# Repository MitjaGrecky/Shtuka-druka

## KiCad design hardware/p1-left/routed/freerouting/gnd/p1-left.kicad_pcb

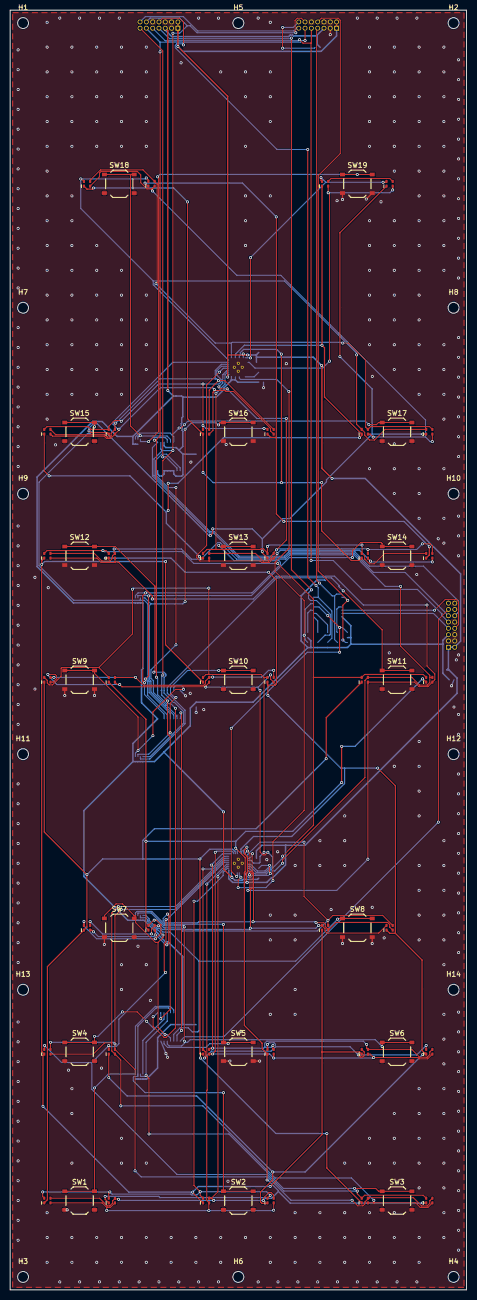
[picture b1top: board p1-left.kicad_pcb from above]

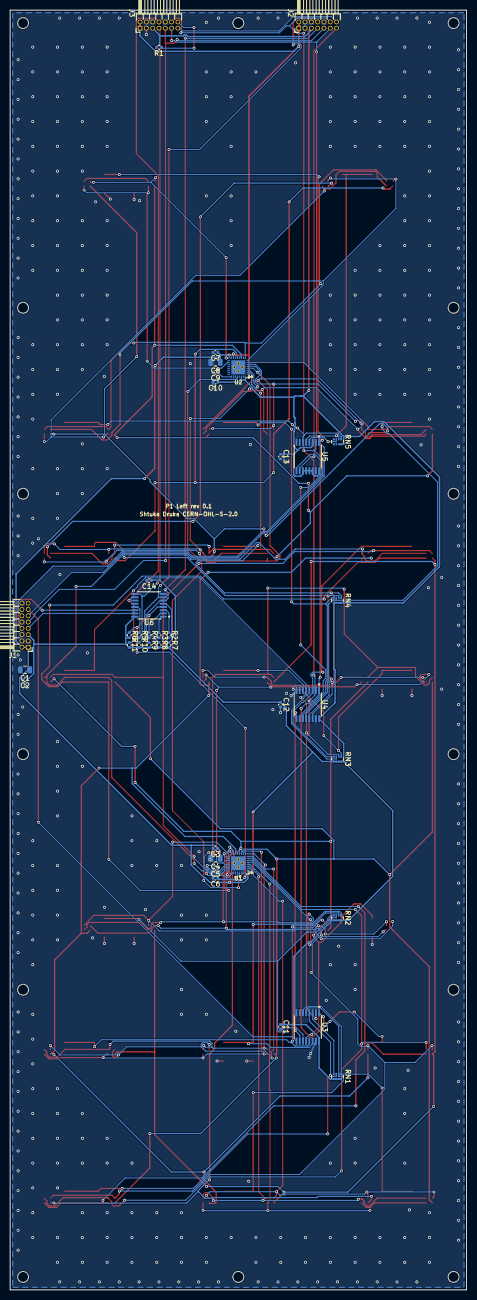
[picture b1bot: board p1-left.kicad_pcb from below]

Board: 2 copper layers, 92.0 x 258.0 mm, 110 parts (39 on the bottom side), 83 nets.

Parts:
C1: 10u; C_0805_2012Metric
C2, C3, C5, C7, C9: 1u; C_0402_1005Metric
C4, C8: 4.7u; C_0805_2012Metric
C6, C10: 1n; C_0402_1005Metric
C11, C12, C13, C14: 100n; C_0402_1005Metric
D1, D2, D3, D4, D5, D6, D7, D8, D9, D10, D11, D12, D13, D14, D15, D16, D17, D18, D19, D20, D21, D22, D23, D24, D25, D26, D27, D28, D29, D30, D31, D32, D33, D34, D35, D36, D37, D38: XL-1615RGBC-RF; LED_RGB_XL-1615RGBC_1.6x1.5mm
H1, H2, H3, H4, H5, H6, H7, H8, H9, H10, H11, H12, H13, H14: M2; MountingHole_2.2mm_M2
J1: Deck bus to P2 2x8 1.27; PinHeader_2x08_P1.27mm_Horizontal
J2: Module bus to M3 2x7 1.27; PinHeader_2x07_P1.27mm_Horizontal
J3: Module bus to W1 2x7 1.27; PinHeader_2x07_P1.27mm_Horizontal
R1, R2: 10k; R_0402_1005Metric
R3, R4, R5: 0; R_0402_1005Metric
R6, R7, R8, R9, R10, R11: 4.7k; R_0402_1005Metric
RN1, RN2, RN3, RN4, RN5: 4x10k; R_Array_Convex_4x0402
SW1, SW2, SW3, SW4, SW5, SW6, SW7, SW8, SW9, SW10, SW11, SW12, SW13, SW14, SW15, SW16, SW17, SW18, SW19: TS-1187A-B-A-B; SW_Push_1P1T_XKB_TS-1187A
U1, U2: LP5864RSMR; VQFN-32-1EP_4x4mm_P0.4mm_EP2.8x2.8mm
U3, U4, U5: 74HC165PW; TSSOP-16_4.4x5mm_P0.65mm
U6: TCA9546APWR; TSSOP-16_4.4x5mm_P0.65mm

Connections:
+3V3: C2.1, C6.1, C10.1, C11.1, C12.1, C13.1, C14.1, J1.5, J2.5, J3.5, R1.2, R2.2, R6.2, R7.2, R8.2, R9.2, R10.2, R11.2, RN1.5, RN1.6, RN1.7, RN1.8, RN2.5, RN2.6, RN2.7, RN2.8, RN3.5, RN3.6, RN3.7, RN3.8, RN4.5, RN4.6, RN4.7, RN4.8, RN5.6, RN5.7, RN5.8, U1.32, U2.30, U2.32, U3.16, U4.16, U5.3, U5.11, U5.12, U5.13, U5.14, U5.16, U6.16
+5V: C1.1, C3.1, C4.1, C7.1, C8.1, J1.1, J1.2, J2.1, J2.2, J3.1, J3.2, U1.1, U1.15, U2.1, U2.15
/A_CS0: D1.1, D2.1, D3.1, D4.1, U1.2
/A_CS1: D1.3, D2.3, D3.3, D4.3, U1.3
/A_CS2: D1.4, D2.4, D3.4, D4.4, U1.4
/A_CS3: D5.1, D6.1, D7.1, D8.1, U1.5
/A_CS4: D5.3, D6.3, D7.3, D8.3, U1.6
/A_CS5: D5.4, D6.4, D7.4, D8.4, U1.7
/A_CS6: D9.1, D10.1, D11.1, D12.1, U1.8
/A_CS7: D9.3, D10.3, D11.3, D12.3, U1.9
/A_CS8: D9.4, D10.4, D11.4, D12.4, U1.10
/A_CS9: D13.1, D14.1, D15.1, D16.1, U1.16
/A_CS10: D13.3, D14.3, D15.3, D16.3, U1.17
/A_CS11: D13.4, D14.4, D15.4, D16.4, U1.18
/A_CS12: D17.1, D18.1, D19.1, D20.1, U1.19
/A_CS13: D17.3, D18.3, D19.3, D20.3, U1.20
/A_CS14: D17.4, D18.4, D19.4, D20.4, U1.21
/A_CS15: D21.1, D22.1, D23.1, D24.1, U1.22
/A_CS16: D21.3, D22.3, D23.3, D24.3, U1.23
/A_CS17: D21.4, D22.4, D23.4, D24.4, U1.24
/A_SW0: D1.2, D5.2, D9.2, D13.2, D17.2, D21.2, U1.11
/A_SW1: D2.2, D6.2, D10.2, D14.2, D18.2, D22.2, U1.12
/A_SW2: D3.2, D7.2, D11.2, D15.2, D19.2, D23.2, U1.13
/A_SW3: D4.2, D8.2, D12.2, D16.2, D20.2, D24.2, U1.14
/A_VCAP: C5.1, U1.25
/BTN1: RN1.1, SW1.1, U3.6
/BTN2: RN1.2, SW2.1, U3.5
/BTN3: RN1.3, SW3.1, U3.4
/BTN4: RN1.4, SW4.1, U3.3
/BTN5: RN2.1, SW5.1, U3.14
/BTN6: RN2.2, SW6.1, U3.13
/BTN7: RN2.3, SW7.1, U3.12
/BTN8: RN2.4, SW8.1, U3.11
/BTN9: RN3.1, SW9.1, U4.6
/BTN10: RN3.2, SW10.1, U4.5
/BTN11: RN3.3, SW11.1, U4.4
/BTN12: RN3.4, SW12.1, U4.3
/BTN13: RN4.1, SW13.1, U4.14
/BTN14: RN4.2, SW14.1, U4.13
/BTN15: RN4.3, SW15.1, U4.12
/BTN16: RN4.4, SW16.1, U4.11
/BTN17: RN5.1, SW17.1, U5.6
/BTN18: RN5.2, SW18.1, U5.5
/BTN19: RN5.3, SW19.1, U5.4
/B_CS0: D25.1, D26.1, D27.1, D28.1, U2.2
/B_CS1: D25.3, D26.3, D27.3, D28.3, U2.3
/B_CS2: D25.4, D26.4, D27.4, D28.4, U2.4
/B_CS3: D29.1, D30.1, D31.1, D32.1, U2.5
/B_CS4: D29.3, D30.3, D31.3, D32.3, U2.6
/B_CS5: D29.4, D30.4, D31.4, D32.4, U2.7
/B_CS6: D33.1, D34.1, D35.1, D36.1, U2.8
/B_CS7: D33.3, D34.3, D35.3, D36.3, U2.9
/B_CS8: D33.4, D34.4, D35.4, D36.4, U2.10
/B_CS9: D37.1, D38.1, U2.16
/B_CS10: D37.3, D38.3, U2.17
/B_CS11: D37.4, D38.4, U2.18
/B_SW0: D25.2, D29.2, D33.2, D37.2, U2.11
/B_SW1: D26.2, D30.2, D34.2, D38.2, U2.12
/B_SW2: D27.2, D31.2, D35.2, U2.13
/B_SW3: D28.2, D32.2, D36.2, U2.14
/B_VCAP: C9.1, U2.25
/MUX_A0: R3.1, U6.1
/MUX_A1: R4.1, U6.2
/MUX_A2: R5.1, U6.13
/MUX_RST: R2.1, U6.3
/SC0: R7.1, U1.28, U2.28, U6.5
/SC1: J2.8, R9.1, U6.7
/SC2: J3.8, R11.1, U6.10
/SCL: J1.8, U6.14
/SD0: R6.1, U1.29, U2.29, U6.4
/SD1: J2.7, R8.1, U6.6
/SD2: J3.7, R10.1, U6.9
/SDA: J1.7, U6.15
/SR_CLK: J1.12, J2.12, J3.12, U3.2, U4.2, U5.2
/SR_END: J3.14, R1.1
/SR_M3: J2.13, U5.10
/SR_OUT: J1.13, U3.9
/SR_Q1: U3.10, U4.9
/SR_Q2: U4.10, U5.9
/SR_W1: J2.14, J3.13
/~INT: J1.9, J2.9, J3.9
/~SR_LOAD: J1.11, J2.11, J3.11, U3.1, U4.1, U5.1
GND: C1.2, C2.2, C3.2, C4.2, C5.2, C6.2, C7.2, C8.2, C9.2, C10.2, C11.2, C12.2, C13.2, C14.2, J1.3, J1.4, J1.6, J1.10, J1.16, J2.3, J2.4, J2.6, J2.10, J3.3, J3.4, J3.6, J3.10, R3.2, R4.2, R5.2, SW1.2, SW2.2, SW3.2, SW4.2, SW5.2, SW6.2, SW7.2, SW8.2, SW9.2, SW10.2, SW11.2, SW12.2, SW13.2, SW14.2, SW15.2, SW16.2, SW17.2, SW18.2, SW19.2, U1.26, U1.27, U1.30, U1.31, U1.33, U2.26, U2.27, U2.31, U2.33, U3.8, U3.15, U4.8, U4.15, U5.8, U5.15, U6.8

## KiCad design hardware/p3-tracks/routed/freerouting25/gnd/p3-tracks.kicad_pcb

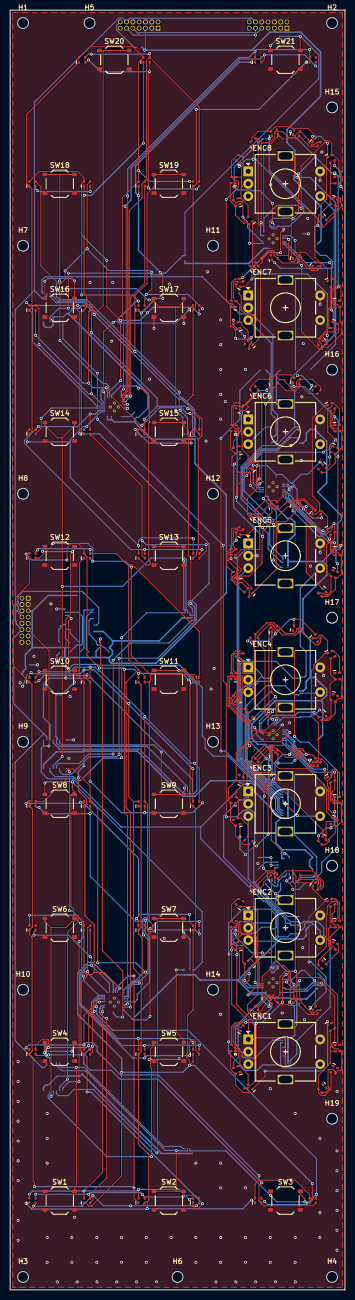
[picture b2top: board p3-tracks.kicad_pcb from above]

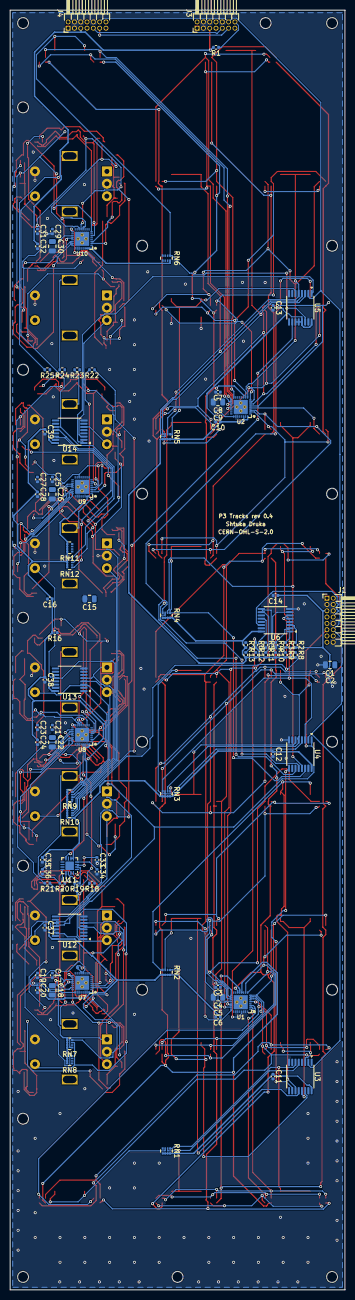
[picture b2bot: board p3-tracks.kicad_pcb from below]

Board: 4 copper layers, 67.5 x 258.0 mm, 276 parts (90 on the bottom side), 226 nets.

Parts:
C1, C15: 10u; C_0805_2012Metric
C2, C3, C5, C7, C9, C16, C17, C19, C21, C23, C25, C27, C29, C31, C35: 1u; C_0402_1005Metric
C4, C8, C18, C22, C26, C30: 4.7u; C_0805_2012Metric
C6, C10, C20, C24, C28, C32: 1n; C_0402_1005Metric
C11, C12, C13, C14, C34, C36, C37, C38, C39: 100n; C_0402_1005Metric
C33: 2.2n; C_0402_1005Metric
D1, D2, D3, D4, D5, D6, D7, D8, D9, D10, D11, D12, D13, D14, D15, D16, D17, D18, D19, D20, D21, D22, D23, D24, D25, D26, D27, D28, D29, D30, D31, D32, D33, D34, D35, D36, D37, D38, D39, D40, D41, D42, D43, D44, D45, D46, D47, D48, D49, D50, D51, D52, D53, D54, D55, D56, D57, D58, D59, D60, D61, D62, D63, D64, D65, D66, D67, D68, D69, D70, D71, D72, D73, D74, D75, D76, D77, D78, D79, D80, D81, D82, D83, D84, D85, D86, D87, D88, D89, D90, D91, D92, D93, D94, D95, D96, D97, D98, D99, D100, D101, D102, D103, D104, D105, D106, D107, D108, D109, D110, D111, D112, D113, D114, D115, D116, D117, D118, D119, D120, D121, D122, D123, D124, D125, D126, D127, D128, D129, D130, D131, D132, D133, D134, D135, D136, D137, D138: XL-1615RGBC-RF; LED_RGB_XL-1615RGBC_1.6x1.5mm
ENC1, ENC2, ENC3, ENC4, ENC5, ENC6, ENC7, ENC8: EC11E smooth, switch; RotaryEncoder_Alps_EC11E-Switch_Vertical_H20mm_Ring
H1, H2, H3, H4, H5, H6, H7, H8, H9, H10, H11, H12, H13, H14, H15, H16, H17, H18, H19: M2; MountingHole_2.2mm_M2
J1: Deck bus to P2 2x8 1.27; PinHeader_2x08_P1.27mm_Horizontal
J3: Module bus to M4 2x7 1.27; PinHeader_2x07_P1.27mm_Horizontal
J4: Module bus to W2 2x7 1.27; PinHeader_2x07_P1.27mm_Horizontal
R1, R2, R16: 10k; R_0402_1005Metric
R3, R4, R5: 0; R_0402_1005Metric
R6, R7, R8, R9, R10, R11, R12, R13: 4.7k; R_0402_1005Metric
R18, R19, R20, R21, R22, R23, R24, R25: 560; R_0402_1005Metric
RN1, RN2, RN3, RN4, RN5, RN6, RN7, RN8, RN9, RN10, RN11, RN12: 4x10k; R_Array_Convex_4x0402
SW1, SW2, SW3, SW4, SW5, SW6, SW7, SW8, SW9, SW10, SW11, SW12, SW13, SW14, SW15, SW16, SW17, SW18, SW19, SW20, SW21: TS-1187A-B-A-B; SW_Push_1P1T_XKB_TS-1187A
U1, U2, U7, U8, U9, U10: LP5864RSMR; VQFN-32-1EP_4x4mm_P0.4mm_EP2.8x2.8mm
U3, U4, U5, U12, U13, U14: 74HC165PW; TSSOP-16_4.4x5mm_P0.65mm
U6: TCA9546APWR; TSSOP-16_4.4x5mm_P0.65mm
U11: CY8CMBR3108-LQXIT; QFN-16-1EP_3x3mm_P0.5mm_EP1.7x1.7mm

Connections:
+3V3: C2.1, C6.1, C10.1, C11.1, C12.1, C13.1, C14.1, C16.1, C20.1, C24.1, C28.1, C32.1, C35.1, C36.1, C37.1, C38.1, C39.1, J1.5, J3.5, J4.5, R1.2, R2.2, R3.2, R6.2, R7.2, R8.2, R9.2, R10.2, R11.2, R12.2, R13.2, R16.2, RN1.5, RN1.6, RN1.7, RN1.8, RN2.5, RN2.6, RN2.7, RN2.8, RN3.5, RN3.6, RN3.7, RN3.8, RN4.5, RN4.6, RN4.7, RN4.8, RN5.5, RN5.6, RN5.7, RN5.8, RN6.8, RN7.5, RN7.6, RN7.7, RN7.8, RN8.5, RN8.6, RN8.7, RN8.8, RN9.5, RN9.6, RN9.7, RN9.8, RN10.5, RN10.6, RN10.7, RN10.8, RN11.5, RN11.6, RN11.7, RN11.8, RN12.5, RN12.6, RN12.7, RN12.8, U1.32, U2.30, U2.32, U3.16, U4.16, U5.11, U5.12, U5.13, U5.16, U6.16, U7.32, U8.30, U8.32, U9.31, U9.32, U10.30, U10.31, U10.32, U11.5, U11.6, U12.16, U13.16, U14.16
+5V: C1.1, C3.1, C4.1, C7.1, C8.1, C15.1, C17.1, C18.1, C21.1, C22.1, C25.1, C26.1, C29.1, C30.1, J1.1, J1.2, J3.1, J3.2, J4.1, J4.2, U1.1, U1.15, U2.1, U2.15, U7.1, U7.15, U8.1, U8.15, U9.1, U9.15, U10.1, U10.15
/A_CS0: D1.1, D2.1, D3.1, D4.1, U1.2
/A_CS1: D1.4, D2.4, D3.4, D4.4, U1.3
/A_CS2: D1.3, D2.3, D3.3, D4.3, U1.4
/A_CS3: D5.1, D6.1, D7.1, D8.1, U1.5
/A_CS4: D5.4, D6.4, D7.4, D8.4, U1.6
/A_CS5: D5.3, D6.3, D7.3, D8.3, U1.7
/A_CS6: D9.1, D10.1, D11.1, D12.1, U1.8
/A_CS7: D9.4, D10.4, D11.4, D12.4, U1.9
/A_CS8: D9.3, D10.3, D11.3, D12.3, U1.10
/A_CS9: D13.1, D14.1, D15.1, D16.1, U1.16
/A_CS10: D13.4, D14.4, D15.4, D16.4, U1.17
/A_CS11: D13.3, D14.3, D15.3, D16.3, U1.18
/A_CS12: D17.1, D18.1, D19.1, D20.1, U1.19
/A_CS13: D17.4, D18.4, D19.4, D20.4, U1.20
/A_CS14: D17.3, D18.3, D19.3, D20.3, U1.21
/A_CS15: D21.1, D22.1, D23.1, D24.1, U1.22
/A_CS16: D21.4, D22.4, D23.4, D24.4, U1.23
/A_CS17: D21.3, D22.3, D23.3, D24.3, U1.24
/A_SW0: D1.2, D5.2, D9.2, D13.2, D17.2, D21.2, U1.11
/A_SW1: D2.2, D6.2, D10.2, D14.2, D18.2, D22.2, U1.12
/A_SW2: D3.2, D7.2, D11.2, D15.2, D19.2, D23.2, U1.13
/A_SW3: D4.2, D8.2, D12.2, D16.2, D20.2, D24.2, U1.14
/A_VCAP: C5.1, U1.25
/BTN1: RN1.1, SW1.1, U3.6
/BTN2: RN1.2, SW2.1, U3.5
/BTN3: RN1.3, SW3.1, U3.4
/BTN4: RN1.4, SW4.1, U3.3
/BTN5: RN2.1, SW5.1, U3.14
/BTN6: RN2.2, SW6.1, U3.13
/BTN7: RN2.3, SW7.1, U3.12
/BTN8: RN2.4, SW8.1, U3.11
/BTN9: RN3.1, SW9.1, U4.6
/BTN10: RN3.2, SW10.1, U4.5
/BTN11: RN3.3, SW11.1, U4.4
/BTN12: RN3.4, SW12.1, U4.3
/BTN13: RN4.1, SW13.1, U4.14
/BTN14: RN4.2, SW14.1, U4.13
/BTN15: RN4.3, SW15.1, U4.12
/BTN16: RN4.4, SW16.1, U4.11
/BTN17: RN5.1, SW17.1, U5.6
/BTN18: RN5.2, SW18.1, U5.5
/BTN19: RN5.3, SW19.1, U5.4
/BTN20: RN5.4, SW20.1, U5.3
/BTN21: RN6.1, SW21.1, U5.14
/B_CS0: D25.1, D26.1, D27.1, D28.1, U2.2
/B_CS1: D25.4, D26.4, D27.4, D28.4, U2.3
/B_CS2: D25.3, D26.3, D27.3, D28.3, U2.4
/B_CS3: D29.1, D30.1, D31.1, D32.1, U2.5
/B_CS4: D29.4, D30.4, D31.4, D32.4, U2.6
/B_CS5: D29.3, D30.3, D31.3, D32.3, U2.7
/B_CS6: D33.1, D34.1, D35.1, D36.1, U2.8
/B_CS7: D33.4, D34.4, D35.4, D36.4, U2.9
/B_CS8: D33.3, D34.3, D35.3, D36.3, U2.10
/B_CS9: D37.1, D38.1, D39.1, D40.1, U2.16
/B_CS10: D37.4, D38.4, D39.4, D40.4, U2.17
/B_CS11: D37.3, D38.3, D39.3, D40.3, U2.18
/B_CS12: D41.1, D42.1, U2.19
/B_CS13: D41.4, D42.4, U2.20
/B_CS14: D41.3, D42.3, U2.21
/B_SW0: D25.2, D29.2, D33.2, D37.2, D41.2, U2.11
/B_SW1: D26.2, D30.2, D34.2, D38.2, D42.2, U2.12
/B_SW2: D27.2, D31.2, D35.2, D39.2, U2.13
/B_SW3: D28.2, D32.2, D36.2, D40.2, U2.14
/B_VCAP: C9.1, U2.25
/CMOD: C33.1, U11.3
/E0_A: ENC1.A, RN7.1, U12.6
/E0_B: ENC1.B, RN7.2, U12.5
/E0_SW: ENC1.S1, RN7.3, U12.4
/E1_A: ENC2.A, RN7.4, U12.3
/E1_B: ENC2.B, RN8.1, U12.14
/E1_SW: ENC2.S1, RN8.2, U12.13
/E2_A: ENC3.A, RN8.3, U12.12
/E2_B: ENC3.B, RN8.4, U12.11
/E2_SW: ENC3.S1, RN9.1, U13.6
/E3_A: ENC4.A, RN9.2, U13.5
/E3_B: ENC4.B, RN9.3, U13.4
/E3_SW: ENC4.S1, RN9.4, U13.3
/E4_A: ENC5.A, RN10.1, U13.14
/E4_B: ENC5.B, RN10.2, U13.13
/E4_SW: ENC5.S1, RN10.3, U13.12
/E5_A: ENC6.A, RN10.4, U13.11
/E5_B: ENC6.B, RN11.1, U14.6
/E5_SW: ENC6.S1, RN11.2, U14.5
/E6_A: ENC7.A, RN11.3, U14.4
/E6_B: ENC7.B, RN11.4, U14.3
/E6_SW: ENC7.S1, RN12.1, U14.14
/E7_A: ENC8.A, RN12.2, U14.13
/E7_B: ENC8.B, RN12.3, U14.12
/E7_SW: ENC8.S1, RN12.4, U14.11
/LA_CS0: D55.1, D56.1, D57.1, D58.1, U7.2
/LA_CS1: D55.4, D56.4, D57.4, D58.4, U7.3
/LA_CS2: D55.3, D56.3, D57.3, D58.3, U7.4
/LA_CS3: D59.1, D60.1, D61.1, D62.1, U7.5
/LA_CS4: D59.4, D60.4, D61.4, D62.4, U7.6
/LA_CS5: D59.3, D60.3, D61.3, D62.3, U7.7
/LA_CS6: D63.1, D64.1, D65.1, D66.1, U7.8
/LA_CS7: D63.4, D64.4, D65.4, D66.4, U7.9
/LA_CS8: D63.3, D64.3, D65.3, D66.3, U7.10
/LA_CS9: D43.1, D44.1, D45.1, D46.1, U7.16
/LA_CS10: D43.4, D44.4, D45.4, D46.4, U7.17
/LA_CS11: D43.3, D44.3, D45.3, D46.3, U7.18
/LA_CS12: D47.1, D48.1, D49.1, D50.1, U7.19
/LA_CS13: D47.4, D48.4, D49.4, D50.4, U7.20
/LA_CS14: D47.3, D48.3, D49.3, D50.3, U7.21
/LA_CS15: D51.1, D52.1, D53.1, D54.1, U7.22
/LA_CS16: D51.4, D52.4, D53.4, D54.4, U7.23
/LA_CS17: D51.3, D52.3, D53.3, D54.3, U7.24
/LA_SW0: D43.2, D50.2, D51.2, D55.2, D62.2, D63.2, U7.11
/LA_SW1: D44.2, D49.2, D52.2, D56.2, D61.2, D64.2, U7.12
/LA_SW2: D45.2, D48.2, D53.2, D57.2, D60.2, D65.2, U7.13
/LA_SW3: D46.2, D47.2, D54.2, D58.2, D59.2, D66.2, U7.14
/LA_VCAP: C19.1, U7.25
/LB_CS0: D79.1, D80.1, D81.1, D82.1, U8.2
/LB_CS1: D79.4, D80.4, D81.4, D82.4, U8.3
/LB_CS2: D79.3, D80.3, D81.3, D82.3, U8.4
/LB_CS3: D83.1, D84.1, D85.1, D86.1, U8.5
/LB_CS4: D83.4, D84.4, D85.4, D86.4, U8.6
/LB_CS5: D83.3, D84.3, D85.3, D86.3, U8.7
/LB_CS6: D87.1, D88.1, D89.1, D90.1, U8.8
/LB_CS7: D87.4, D88.4, D89.4, D90.4, U8.9
/LB_CS8: D87.3, D88.3, D89.3, D90.3, U8.10
/LB_CS9: D67.1, D68.1, D69.1, D70.1, U8.16
/LB_CS10: D67.4, D68.4, D69.4, D70.4, U8.17
/LB_CS11: D67.3, D68.3, D69.3, D70.3, U8.18
/LB_CS12: D71.1, D72.1, D73.1, D74.1, U8.19
/LB_CS13: D71.4, D72.4, D73.4, D74.4, U8.20
/LB_CS14: D71.3, D72.3, D73.3, D74.3, U8.21
/LB_CS15: D75.1, D76.1, D77.1, D78.1, U8.22
/LB_CS16: D75.4, D76.4, D77.4, D78.4, U8.23
/LB_CS17: D75.3, D76.3, D77.3, D78.3, U8.24
/LB_SW0: D67.2, D74.2, D75.2, D79.2, D86.2, D87.2, U8.11
/LB_SW1: D68.2, D73.2, D76.2, D80.2, D85.2, D88.2, U8.12
/LB_SW2: D69.2, D72.2, D77.2, D81.2, D84.2, D89.2, U8.13
/LB_SW3: D70.2, D71.2, D78.2, D82.2, D83.2, D90.2, U8.14
/LB_VCAP: C23.1, U8.25
/LC_CS0: D103.1, D104.1, D105.1, D106.1, U9.2
/LC_CS1: D103.4, D104.4, D105.4, D106.4, U9.3
/LC_CS2: D103.3, D104.3, D105.3, D106.3, U9.4
/LC_CS3: D107.1, D108.1, D109.1, D110.1, U9.5
/LC_CS4: D107.4, D108.4, D109.4, D110.4, U9.6
/LC_CS5: D107.3, D108.3, D109.3, D110.3, U9.7
/LC_CS6: D111.1, D112.1, D113.1, D114.1, U9.8
/LC_CS7: D111.4, D112.4, D113.4, D114.4, U9.9
/LC_CS8: D111.3, D112.3, D113.3, D114.3, U9.10
/LC_CS9: D91.1, D92.1, D93.1, D94.1, U9.16
/LC_CS10: D91.4, D92.4, D93.4, D94.4, U9.17
/LC_CS11: D91.3, D92.3, D93.3, D94.3, U9.18
/LC_CS12: D95.1, D96.1, D97.1, D98.1, U9.19
/LC_CS13: D95.4, D96.4, D97.4, D98.4, U9.20
/LC_CS14: D95.3, D96.3, D97.3, D98.3, U9.21
/LC_CS15: D99.1, D100.1, D101.1, D102.1, U9.22
/LC_CS16: D99.4, D100.4, D101.4, D102.4, U9.23
/LC_CS17: D99.3, D100.3, D101.3, D102.3, U9.24
/LC_SW0: D91.2, D98.2, D99.2, D103.2, D110.2, D111.2, U9.11
/LC_SW1: D92.2, D97.2, D100.2, D104.2, D109.2, D112.2, U9.12
/LC_SW2: D93.2, D96.2, D101.2, D105.2, D108.2, D113.2, U9.13
/LC_SW3: D94.2, D95.2, D102.2, D106.2, D107.2, D114.2, U9.14
/LC_VCAP: C27.1, U9.25
/LD_CS0: D127.1, D128.1, D129.1, D130.1, U10.2
/LD_CS1: D127.4, D128.4, D129.4, D130.4, U10.3
/LD_CS2: D127.3, D128.3, D129.3, D130.3, U10.4
/LD_CS3: D131.1, D132.1, D133.1, D134.1, U10.5
/LD_CS4: D131.4, D132.4, D133.4, D134.4, U10.6
/LD_CS5: D131.3, D132.3, D133.3, D134.3, U10.7
/LD_CS6: D135.1, D136.1, D137.1, D138.1, U10.8
/LD_CS7: D135.4, D136.4, D137.4, D138.4, U10.9
/LD_CS8: D135.3, D136.3, D137.3, D138.3, U10.10
/LD_CS9: D115.1, D116.1, D117.1, D118.1, U10.16
/LD_CS10: D115.4, D116.4, D117.4, D118.4, U10.17
/LD_CS11: D115.3, D116.3, D117.3, D118.3, U10.18
/LD_CS12: D119.1, D120.1, D121.1, D122.1, U10.19
/LD_CS13: D119.4, D120.4, D121.4, D122.4, U10.20
/LD_CS14: D119.3, D120.3, D121.3, D122.3, U10.21
/LD_CS15: D123.1, D124.1, D125.1, D126.1, U10.22
/LD_CS16: D123.4, D124.4, D125.4, D126.4, U10.23
/LD_CS17: D123.3, D124.3, D125.3, D126.3, U10.24
/LD_SW0: D115.2, D122.2, D123.2, D127.2, D134.2, D135.2, U10.11
/LD_SW1: D116.2, D121.2, D124.2, D128.2, D133.2, D136.2, U10.12
/LD_SW2: D117.2, D120.2, D125.2, D129.2, D132.2, D137.2, U10.13
/LD_SW3: D118.2, D119.2, D126.2, D130.2, D131.2, D138.2, U10.14
/LD_VCAP: C31.1, U10.25
/MUX_A0: R3.1, U6.1
/MUX_A1: R4.1, U6.2
/MUX_A2: R5.1, U6.13
/MUX_RST: R2.1, U6.3
/SC0: R7.1, U1.28, U2.28, U6.5
/SC1: R9.1, U6.7, U7.28, U8.28, U9.28, U10.28, U11.15
/SC2: J3.8, R11.1, U6.10
/SC3: J4.8, R13.1, U6.12
/SCL: J1.8, U6.14
/SD0: R6.1, U1.29, U2.29, U6.4
/SD1: R8.1, U6.6, U7.29, U8.29, U9.29, U10.29, U11.14
/SD2: J3.7, R10.1, U6.9
/SD3: J4.7, R12.1, U6.11
/SDA: J1.7, U6.15
/SR_CLK: J1.12, J3.12, J4.12, U3.2, U4.2, U5.2, U12.2, U13.2, U14.2
/SR_END: J3.14, R1.1
/SR_L1: U12.10, U13.9
/SR_L2: U13.10, U14.9
/SR_M2: U5.10, U12.9
/SR_M4: J3.13, R16.1, U14.10
/SR_OUT: J1.13, U3.9
/SR_Q1: U3.10, U4.9
/SR_Q2: U4.10, U5.9
/TOUCH0: ENC1.MP, R18.2
/TOUCH1: ENC2.MP, R19.2
/TOUCH2: ENC3.MP, R20.2
/TOUCH3: ENC4.MP, R21.2
/TOUCH4: ENC5.MP, R22.2
/TOUCH5: ENC6.MP, R23.2
/TOUCH6: ENC7.MP, R24.2
/TOUCH7: ENC8.MP, R25.2
/TR0: R18.1, U11.1
/TR1: R19.1, U11.2
/TR2: R20.1, U11.12
/TR3: R21.1, U11.13
/TR4: R22.1, U11.8
/TR5: R23.1, U11.9
/TR6: R24.1, U11.10
/TR7: R25.1, U11.11
/VREG: C34.1, U11.4
/~INT: J1.9, J3.9, J4.9, U11.16
/~SR_LOAD: J1.11, J3.11, J4.11, U3.1, U4.1, U5.1, U12.1, U13.1, U14.1
GND: C1.2, C2.2, C3.2, C4.2, C5.2, C6.2, C7.2, C8.2, C9.2, C10.2, C11.2, C12.2, C13.2, C14.2, C15.2, C16.2, C17.2, C18.2, C19.2, C20.2, C21.2, C22.2, C23.2, C24.2, C25.2, C26.2, C27.2, C28.2, C29.2, C30.2, C31.2, C32.2, C33.2, C34.2, C35.2, C36.2, C37.2, C38.2, C39.2, ENC1.C, ENC1.S2, ENC2.C, ENC2.S2, ENC3.C, ENC3.S2, ENC4.C, ENC4.S2, ENC5.C, ENC5.S2, ENC6.C, ENC6.S2, ENC7.C, ENC7.S2, ENC8.C, ENC8.S2, J1.3, J1.4, J1.6, J1.10, J1.16, J3.3, J3.4, J3.6, J3.10, J4.3, J4.4, J4.6, J4.10, R4.2, R5.2, SW1.2, SW2.2, SW3.2, SW4.2, SW5.2, SW6.2, SW7.2, SW8.2, SW9.2, SW10.2, SW11.2, SW12.2, SW13.2, SW14.2, SW15.2, SW16.2, SW17.2, SW18.2, SW19.2, SW20.2, SW21.2, U1.26, U1.27, U1.30, U1.31, U1.33, U2.26, U2.27, U2.31, U2.33, U3.8, U3.15, U4.8, U4.15, U5.8, U5.15, U6.8, U7.26, U7.27, U7.30, U7.31, U7.33, U8.26, U8.27, U8.31, U8.33, U9.26, U9.27, U9.30, U9.33, U10.26, U10.27, U10.33, U11.7, U11.17, U12.8, U12.15, U13.8, U13.15, U14.8, U14.15

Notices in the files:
hardware/p1-left/routed/freerouting/gnd/p1-left.kicad_pcb:
Shtuka Druka - open hardware, CERN-OHL-S-2.0
Shtuka Druka CERN-OHL-S-2.0
hardware/p3-tracks/routed/freerouting25/gnd/p3-tracks.kicad_pcb:
CERN-OHL-S-2.0
